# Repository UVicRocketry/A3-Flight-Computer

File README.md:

# A3-Flight-Computer
Hardware and software for Anduril-3 flight computer.

## Hardware 
All hardware is designed in KiCAD. If any footprints are added create a folder with the component name in the component-library folder and export all the files to there. when importing footprints and symbols add them to the A3-Flight-Computer library in KiCAD A3 Also add any datasheet and relevent documentation to this folder. 

## Software
All software will be stored in the A3-Flight-Computer-Software. (Rest of Organization TBD)

Various resources such as application notes, various datasheets etc will be stored in the resource folder

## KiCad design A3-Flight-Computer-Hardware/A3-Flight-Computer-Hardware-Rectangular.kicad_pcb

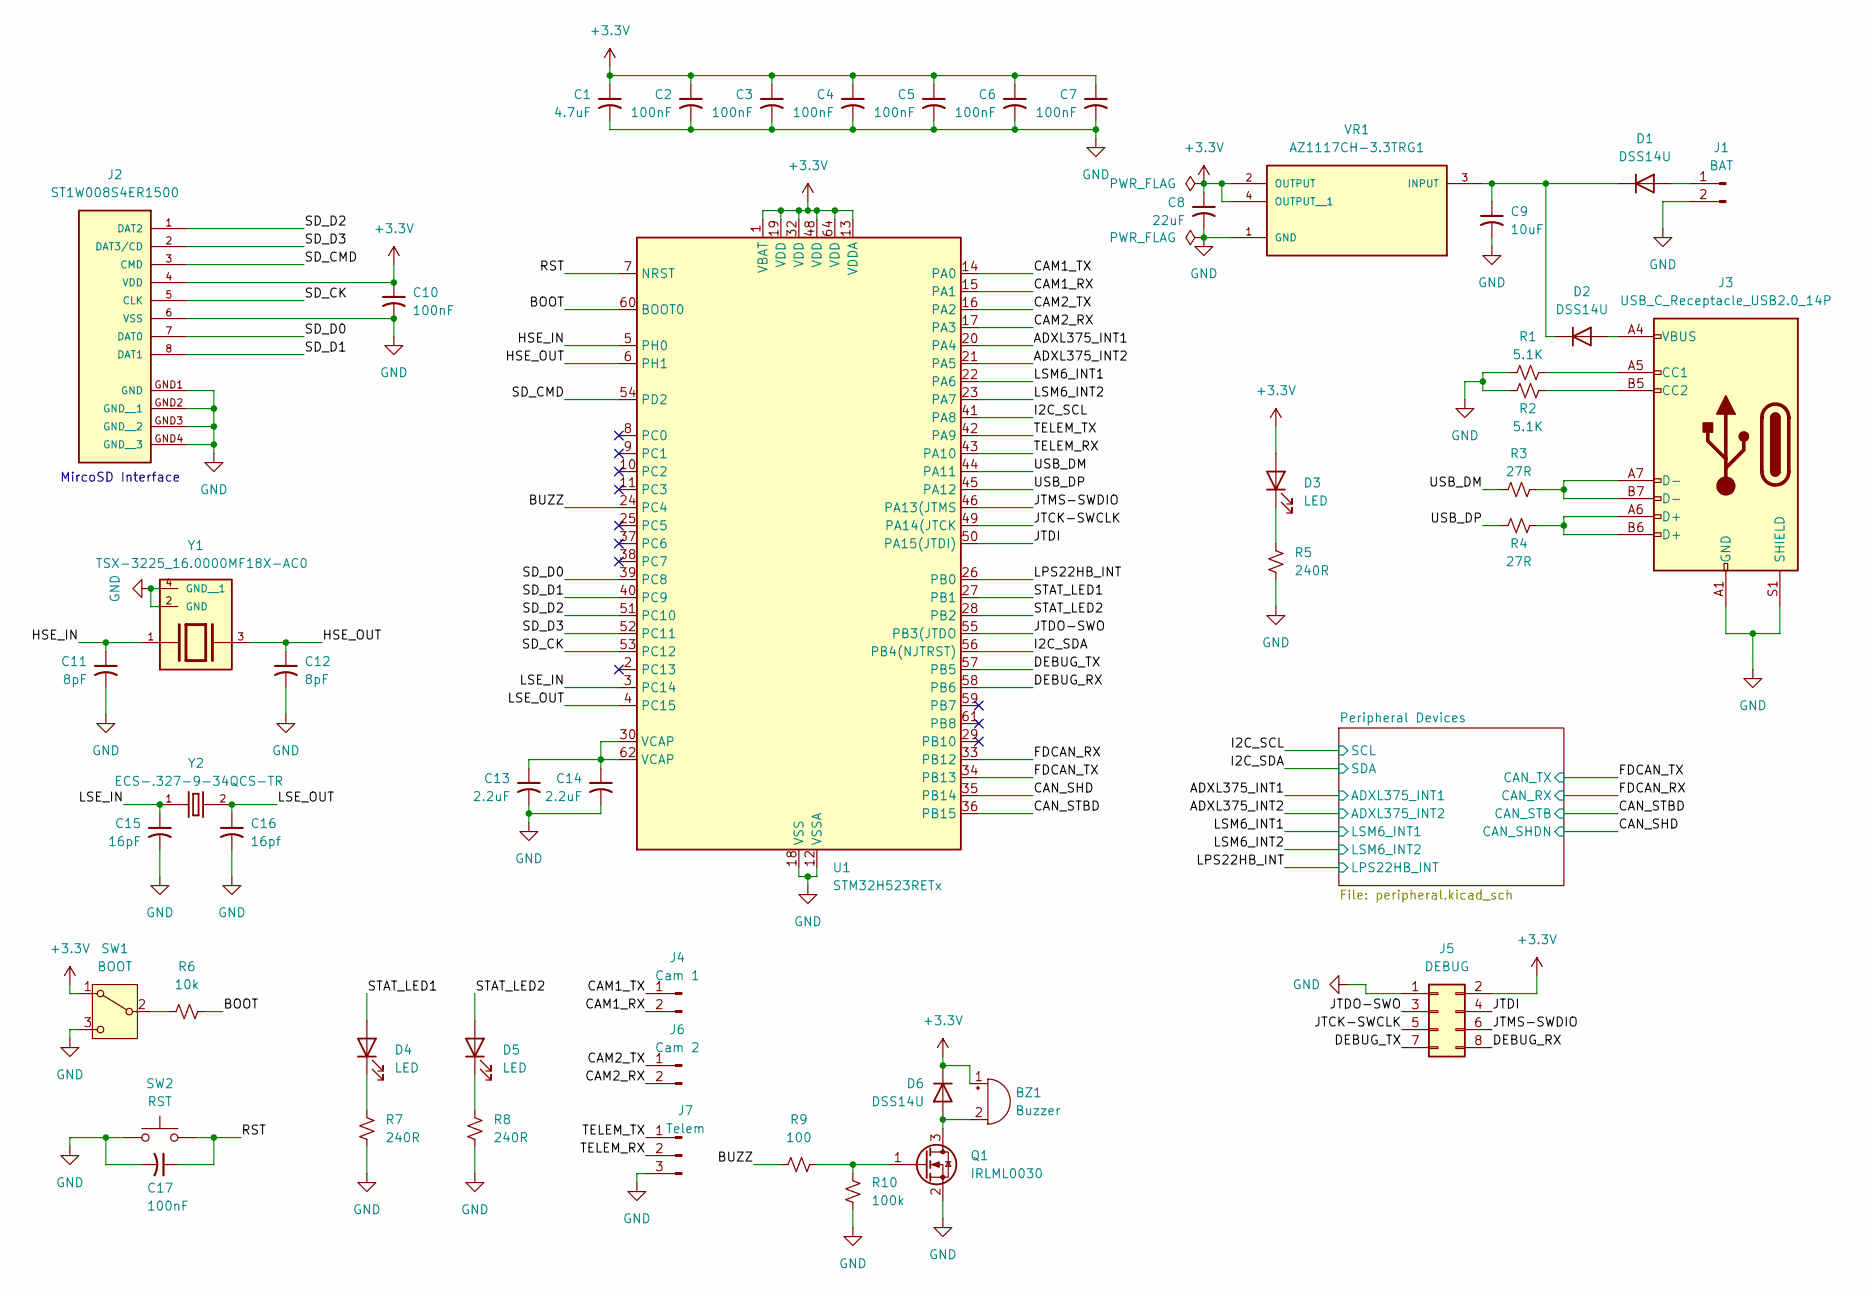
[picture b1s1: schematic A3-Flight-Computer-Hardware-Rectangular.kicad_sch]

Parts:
BZ1: Buzzer; Buzzer_Murata_PKMCS0909E
C1: 4.7uF; C_0805_2012Metric
C2, C3, C4, C5, C6, C7, C10, C17: 100nF; C_0402_1005Metric
C8: 22uF; C_0805_2012Metric
C9: 10uF; C_0805_2012Metric
C11, C12: 8pF; C_0402_1005Metric
C13, C14: 2.2uF; C_0402_1005Metric
C15: 16pF; C_0402_1005Metric
C16: 16pf; C_0402_1005Metric
D1, D2, D6: DSS14U; D_SOD-123
D3, D4, D5: LED; LED_0805_2012Metric_Pad1.15x1.40mm_HandSolder
J1: BAT; JST_XH_S2B-XH-A_1x02_P2.50mm_Horizontal
J2: ST1W008S4ER1500; JAE_ST1W008S4ER1500; PARTREV 2
J3: USB_C_Receptacle_USB2.0_14P; USB_C_Receptacle_Palconn_UTC16-G
J4: Cam 1; JST_XH_S2B-XH-A_1x02_P2.50mm_Horizontal
J5: DEBUG; PinHeader_2x04_P2.54mm_Vertical
J6: Cam 2; JST_XH_S2B-XH-A_1x02_P2.50mm_Horizontal
J7: Telem; JST_XH_S3B-XH-A_1x03_P2.50mm_Horizontal
Q1: IRLML0030; SOT-23
R1, R2: 5.1K; R_0402_1005Metric
R3, R4: 27R; R_0402_1005Metric
R5, R7, R8: 240R; R_0402_1005Metric
R6: 10k; R_0402_1005Metric
R9: 100; R_0402_1005Metric
R10: 100k; R_0402_1005Metric
SW1: BOOT; SW_SPDT_CK_JS102011SAQN
SW2: RST; SW_SPST_TS-1088-xR025
U1: STM32H523RETx; LQFP-64_10x10mm_P0.5mm
VR1: AZ1117CH-3.3TRG1; VREG_AZ1117CH-3.3TRG1; PARTREV 5 - 2
Y1: TSX-3225_16.0000MF18X-AC0; XTAL_TSX-3225_16.0000MF18X-AC0; PARTREV N/A
Y2: ECS-.327-9-34QCS-TR; XTAL_ECS-.327-9-34QCS-TR; PARTREV 2018

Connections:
+3.3V: BZ1.1 (+), C1.1, C2.1, C3.1, C4.1, C5.1, C6.1, C7.1, C8.1, C10.1, D3.2 (A), D6.1 (K), J2.4 (VDD), J5.2, SW1.1 (A), U1.1 (VBAT), U1.13 (VDDA), U1.19 (VDD), U1.32 (VDD), U1.48 (VDD), U1.64 (VDD), VR1.2 (OUTPUT), VR1.4 (OUTPUT__1); also elsewhere on the board
/ADXL375_INT1: U1.20 (PA4); also elsewhere on the board
/ADXL375_INT2: U1.21 (PA5); also elsewhere on the board
/BOOT: R6.2, U1.60 (BOOT0)
/BUZZ: R9.1, U1.24 (PC4)
/CAM1_RX: J4.2, U1.15 (PA1)
/CAM1_TX: J4.1, U1.14 (PA0)
/CAM2_RX: J6.2, U1.17 (PA3)
/CAM2_TX: J6.1, U1.16 (PA2)
/CAN_SHD: U1.35 (PB14); also elsewhere on the board
/CAN_STBD: U1.36 (PB15); also elsewhere on the board
/DEBUG_RX: J5.8, U1.58 (PB6)
/DEBUG_TX: J5.7, U1.57 (PB5)
/FDCAN_RX: U1.33 (PB12); also elsewhere on the board
/FDCAN_TX: U1.34 (PB13); also elsewhere on the board
/HSE_IN: C11.1, U1.5 (PH0), Y1.1
/HSE_OUT: C12.1, U1.6 (PH1), Y1.3
/I2C_SCL: U1.41 (PA8); also elsewhere on the board
/I2C_SDA: U1.56 (PB4(NJTRST)); also elsewhere on the board
/JTCK-SWCLK: J5.5, U1.49 (PA14(JTCK)
/JTDI: J5.4, U1.50 (PA15(JTDI))
/JTDO-SWO: J5.3, U1.55 (PB3(JTDO)
/JTMS-SWDIO: J5.6, U1.46 (PA13(JTMS)
/LPS22HB_INT: U1.26 (PB0); also elsewhere on the board
/LSE_IN: C15.1, U1.3 (PC14), Y2.1
/LSE_OUT: C16.1, U1.4 (PC15), Y2.2
/LSM6_INT1: U1.22 (PA6); also elsewhere on the board
/LSM6_INT2: U1.23 (PA7); also elsewhere on the board
/RST: C17.1, SW2.2, U1.7 (NRST)
/SD_CK: J2.5 (CLK), U1.53 (PC12)
/SD_CMD: J2.3 (CMD), U1.54 (PD2)
/SD_D0: J2.7 (DAT0), U1.39 (PC8)
/SD_D1: J2.8 (DAT1), U1.40 (PC9)
/SD_D2: J2.1 (DAT2), U1.51 (PC10)
/SD_D3: J2.2 (DAT3/CD), U1.52 (PC11)
/STAT_LED1: D4.2 (A), U1.27 (PB1)
/STAT_LED2: D5.2 (A), U1.28 (PB2)
/TELEM_RX: J7.2, U1.43 (PA10)
/TELEM_TX: J7.1, U1.42 (PA9)
/USB_DM: R3.1, U1.44 (PA11)
/USB_DP: R4.1, U1.45 (PA12)
GND: C1.2, C2.2, C3.2, C4.2, C5.2, C6.2, C7.2, C8.2, C9.2, C10.2, C11.2, C12.2, C13.2, C14.2, C15.2, C16.2, C17.2, J1.2, J2.6 (VSS), J2.GND1 (GND), J2.GND2 (GND__1), J2.GND3 (GND__2), J2.GND4 (GND__3), J3.A1 (GND), J3.A12 (GND), J3.B1 (GND), J3.B12 (GND), J3.S1 (SHIELD), J5.1, J7.3, Q1.2 (S), R1.1, R2.1, R5.1, R7.1, R8.1, R10.1, SW1.3 (C), SW2.1, U1.12 (VSSA), U1.18 (VSS), U1.31 (VSS), U1.47 (VSS), U1.63 (VSS), VR1.1 (GND), Y1.2 (GND), Y1.4 (GND__1); also elsewhere on the board
unnamed: BZ1.2 (-), D6.2 (A), Q1.3 (D)
unnamed: C13.1, C14.1, U1.30 (VCAP), U1.62 (VCAP)
unnamed: D1.2 (A), J1.1
unnamed: C9.1, D1.1 (K), D2.1 (K), VR1.3 (INPUT)
unnamed: D2.2 (A), J3.A4 (VBUS), J3.A9 (VBUS), J3.B4 (VBUS), J3.B9 (VBUS)
unnamed: D3.1 (K), R5.2
unnamed: D4.1 (K), R7.2
unnamed: D5.1 (K), R8.2
unnamed: J3.A5 (CC1), R1.2
unnamed: J3.B5 (CC2), R2.2
unnamed: J3.A6 (D+), J3.B6 (D+), R4.2
unnamed: J3.A7 (D-), J3.B7 (D-), R3.2
unnamed: Q1.1 (G), R9.2, R10.2
unnamed: R6.1, SW1.2 (B)

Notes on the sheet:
MircoSD Interface

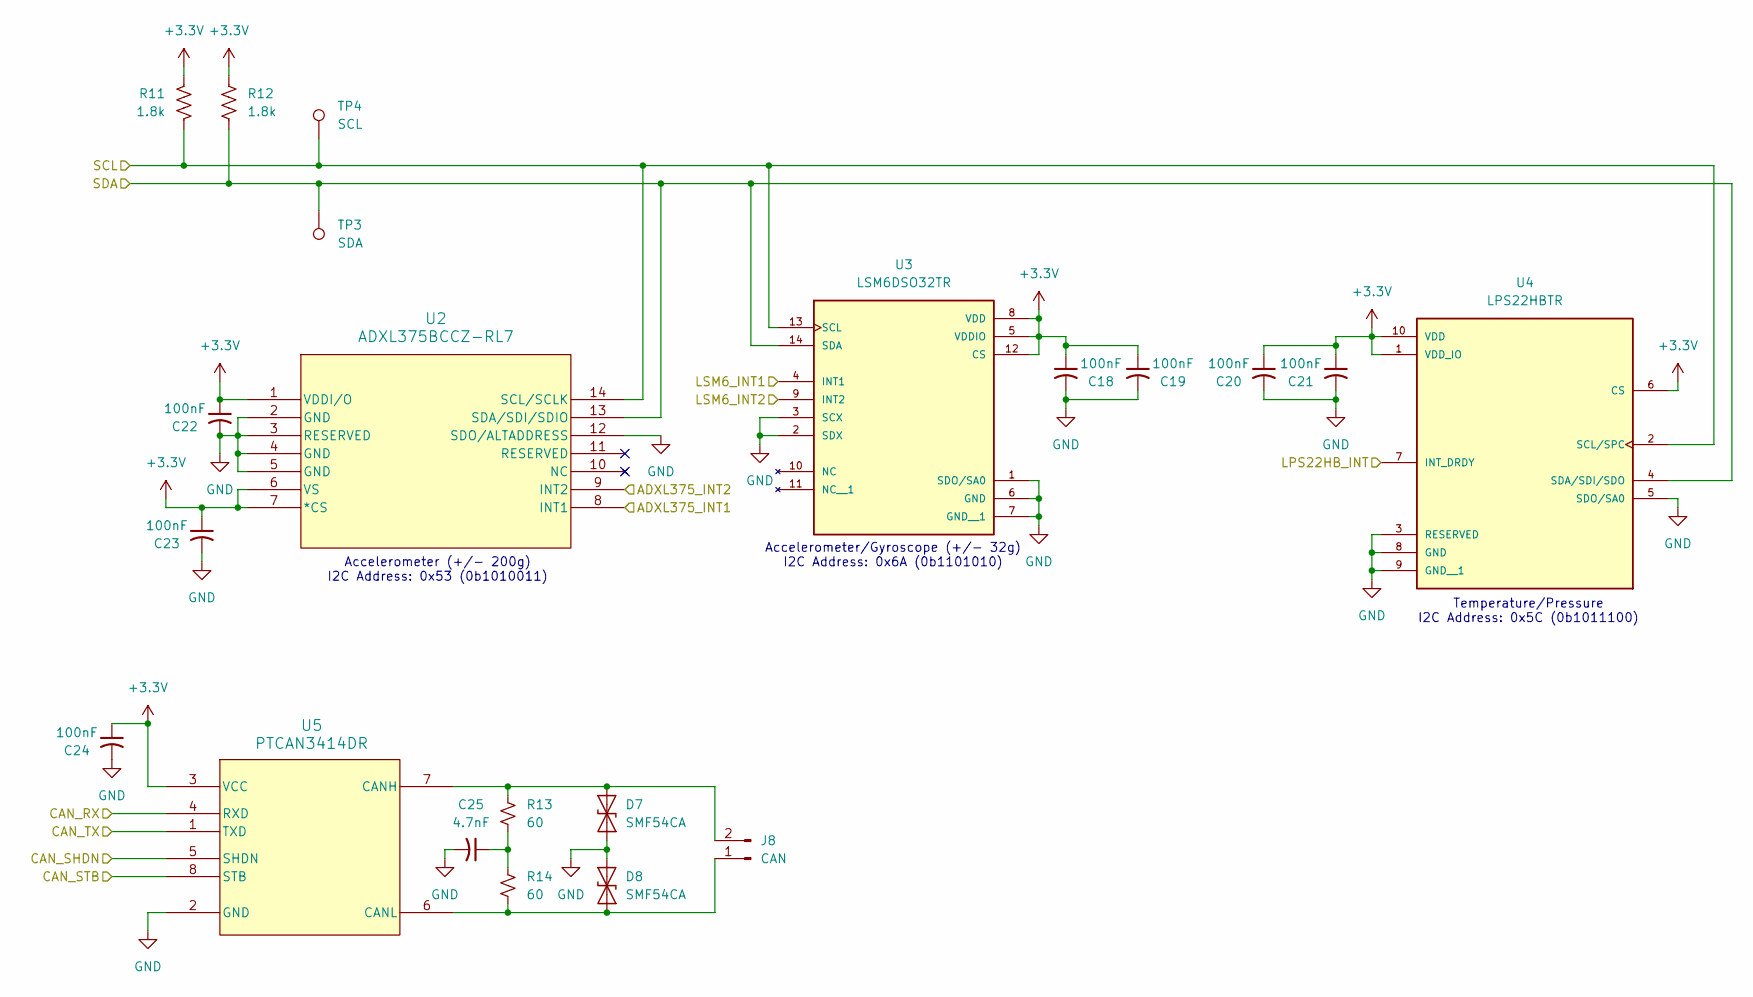
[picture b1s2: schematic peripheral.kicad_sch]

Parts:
C18, C19, C20, C21, C22, C23, C24: 100nF; C_0402_1005Metric
C25: 4.7nF; C_0402_1005Metric
D7, D8: SMF54CA; D_SMF
J8: CAN; JST_XH_S2B-XH-A_1x02_P2.50mm_Horizontal
R11, R12: 1.8k; R_0402_1005Metric
R13, R14: 60; R_0402_1005Metric
TP3: SDA; TestPoint_THTPad_1.0x1.0mm_Drill0.5mm
TP4: SCL; TestPoint_THTPad_1.0x1.0mm_Drill0.5mm
U2: ADXL375BCCZ-RL7; LGA_CC-14-1_ADI
U3: LSM6DSO32TR; XDCR_LSM6DSO32TR; PARTREV 1
U4: LPS22HBTR; PQFN50P200X200X80-10N; PARTREV 6
U5: PTCAN3414DR; SOIC8_D_TEX

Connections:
+3.3V: C18.1, C19.1, C20.1, C21.1, C22.1, C23.1, C24.1, R11.1, R12.1, U2.1 (VDDI/O), U2.6 (VS), U2.7 (*CS), U3.5 (VDDIO), U3.8 (VDD), U3.12 (CS), U4.1 (VDD_IO), U4.6 (CS), U4.10 (VDD), U5.3 (VCC); also elsewhere on the board
/ADXL375_INT1: U2.8 (INT1); also elsewhere on the board
/ADXL375_INT2: U2.9 (INT2); also elsewhere on the board
/CAN_SHD: U5.5 (SHDN); also elsewhere on the board
/CAN_STBD: U5.8 (STB); also elsewhere on the board
/FDCAN_RX: U5.4 (RXD); also elsewhere on the board
/FDCAN_TX: U5.1 (TXD); also elsewhere on the board
/I2C_SCL: R11.2, TP4.1, U2.14 (SCL/SCLK), U3.13 (SCL), U4.2 (SCL/SPC); also elsewhere on the board
/I2C_SDA: R12.2, TP3.1, U2.13 (SDA/SDI/SDIO), U3.14 (SDA), U4.4 (SDA/SDI/SDO); also elsewhere on the board
/LPS22HB_INT: U4.7 (INT_DRDY); also elsewhere on the board
/LSM6_INT1: U3.4 (INT1); also elsewhere on the board
/LSM6_INT2: U3.9 (INT2); also elsewhere on the board
GND: C18.2, C19.2, C20.2, C21.2, C22.2, C23.2, C24.2, C25.2, D7.2 (A2), D8.1 (A1), U2.2 (GND), U2.3 (RESERVED), U2.4 (GND), U2.5 (GND), U2.12 (SDO/ALTADDRESS), U3.1 (SDO/SA0), U3.2 (SDX), U3.3 (SCX), U3.6 (GND), U3.7 (GND__1), U4.3 (RESERVED), U4.5 (SDO/SA0), U4.8 (GND), U4.9 (GND__1), U5.2 (GND); also elsewhere on the board
unnamed: C25.1, R13.1, R14.2
unnamed: D7.1 (A1), J8.2, R13.2, U5.7 (CANH)
unnamed: D8.2 (A2), J8.1, R14.1, U5.6 (CANL)

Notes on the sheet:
Accelerometer (+/- 200g) I2C Address: 0x53 (0b1010011)
Temperature/Pressure I2C Address: 0x5C (0b1011100)
Accelerometer/Gyroscope (+/- 32g) I2C Address: 0x6A (0b1101010)

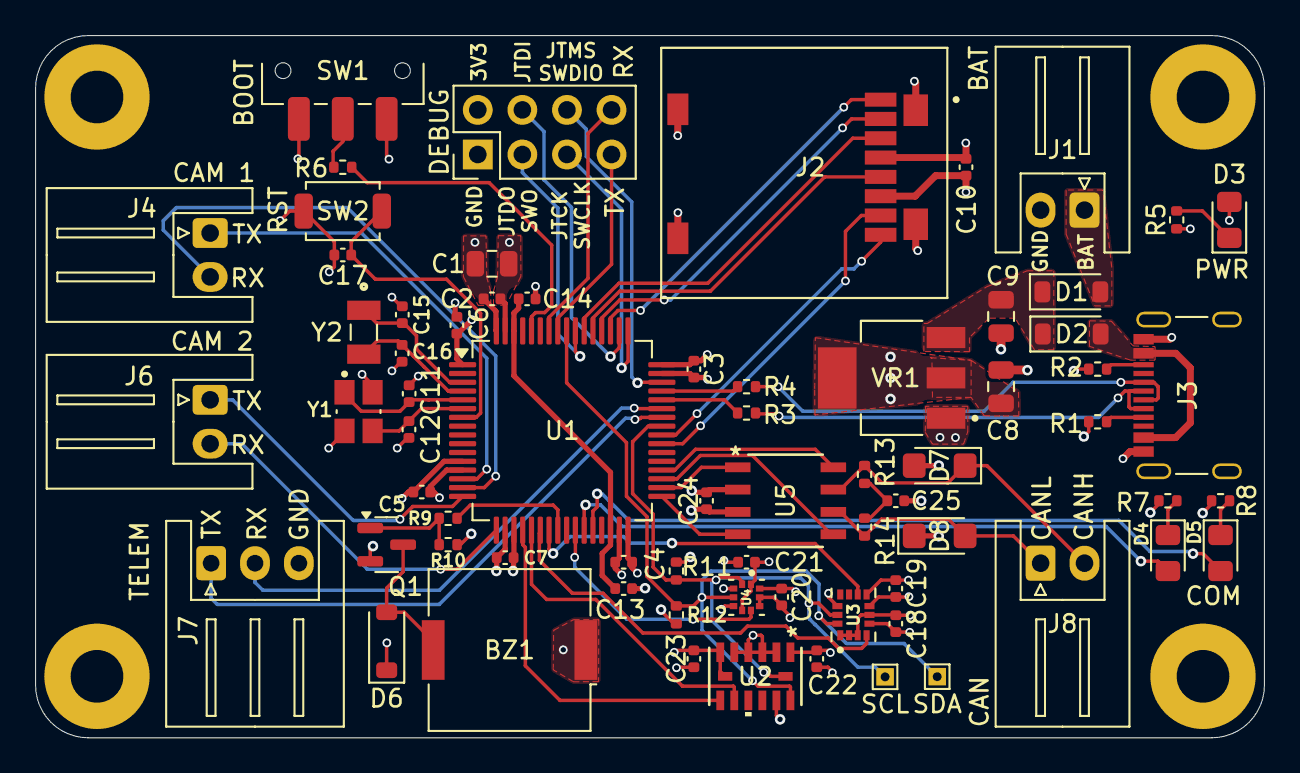
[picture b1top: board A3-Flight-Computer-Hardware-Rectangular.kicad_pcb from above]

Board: 4 copper layers, 70.0 x 40.0 mm, 69 parts (0 on the bottom side), 59 nets.

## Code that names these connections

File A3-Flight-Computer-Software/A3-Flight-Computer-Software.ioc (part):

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Mcu.Name=STM32H523RETx
Mcu.Package=LQFP64
Mcu.UserName=STM32H523RETx
PA10.Signal=USART1_RX
PA11.Mode=Device
PA11.Signal=USB_DM
PA12.Mode=Device
PA12.Signal=USB_DP
PA13(JTMS/SWDIO).Mode=JTAG_4_pins
PA13(JTMS/SWDIO).Signal=DEBUG_JTMS-SWDIO
PA14(JTCK/SWCLK).Mode=JTAG_4_pins
PA14(JTCK/SWCLK).Signal=DEBUG_JTCK-SWCLK
PA15(JTDI).Mode=JTAG_4_pins
PA15(JTDI).Signal=DEBUG_JTDI
PA4.Signal=GPXTI4
PA5.Signal=GPXTI5
PA6.Signal=GPXTI6
PA7.Signal=GPXTI7
PA8.Mode=I2C
PA8.Signal=I2C3_SCL
PA9.Signal=USART1_TX
PB0.Signal=GPXTI0
PB1.Signal=GPIO_Output
PB12.Mode=FDCAN_Activate
PB12.Signal=FDCAN2_RX
PB13.Mode=FDCAN_Activate
PB13.Signal=FDCAN2_TX
PB14.Signal=GPIO_Output
PB15.Signal=GPIO_Output
PB2.Signal=GPIO_Output
PB3(JTDO/TRACESWO).Mode=JTAG_4_pins
PB3(JTDO/TRACESWO).Signal=DEBUG_JTDO-SWO
PB4(NJTRST).Mode=I2C
PB4(NJTRST).Signal=I2C3_SDA
PB5.Signal=UART5_RX
PB6.Signal=UART5_TX
PC10.GPIOParameters=GPIO_PuPd
PC10.GPIO_PuPd=GPIO_PULLUP
PC10.Mode=SD_4_bits_Wide_bus
PC10.Signal=SDMMC1_D2
PC11.GPIOParameters=GPIO_PuPd
PC11.GPIO_PuPd=GPIO_PULLUP
PC11.Mode=SD_4_bits_Wide_bus
PC11.Signal=SDMMC1_D3
PC12.GPIOParameters=GPIO_PuPd
PC12.GPIO_PuPd=GPIO_NOPULL
PC12.Mode=SD_4_bits_Wide_bus
PC12.Signal=SDMMC1_CK
PC13.Mode=Timestamp enabled
PC13.Signal=RTC_TS
PC14-OSC32_IN(OSC32_IN).Mode=LSE-External-Oscillator
PC14-OSC32_IN(OSC32_IN).Signal=RCC_OSC32_IN
PC15-OSC32_OUT(OSC32_OUT).Mode=LSE-External-Oscillator
PC15-OSC32_OUT(OSC32_OUT).Signal=RCC_OSC32_OUT
PC4.Signal=S_TIM2_CH4
PC8.GPIOParameters=GPIO_PuPd
PC8.GPIO_PuPd=GPIO_PULLUP
PC8.Mode=SD_4_bits_Wide_bus
PC8.Signal=SDMMC1_D0
PC9.GPIOParameters=GPIO_PuPd
PC9.GPIO_PuPd=GPIO_PULLUP
PC9.Mode=SD_4_bits_Wide_bus
PC9.Signal=SDMMC1_D1
PD2.GPIOParameters=GPIO_PuPd
PD2.GPIO_PuPd=GPIO_PULLUP
PD2.Mode=SD_4_bits_Wide_bus
PD2.Signal=SDMMC1_CMD
PH0-OSC_IN(PH0).Mode=HSE-External-Oscillator
PH0-OSC_IN(PH0).Signal=RCC_OSC_IN
PH1-OSC_OUT(PH1).Mode=HSE-External-Oscillator
PH1-OSC_OUT(PH1).Signal=RCC_OSC_OUT
RCC.HSE_VALUE=16000000
RCC.SYSCLKFreq_VALUE=250000000
RCC.SYSCLKSource=RCC_SYSCLKSOURCE_PLLCLK
board=custom

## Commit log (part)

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2025-10-24 Expand README with hardware and software sections
    Added sections for hardware and software details.
2025-10-24 Initial Repository Setup
2025-10-29 Initial schematic
2025-11-04 First PCB revision
2025-11-09 Adjusted PCB Dimensions
2025-11-20 Small routing changes
2025-12-07 Added labels and changed component sizes
2026-01-13 Updated gerber files + BOM for purchasing
2026-05-20 Updated STM32CubeMX board Config
2026-05-28 Added FatFs driver
2026-06-20 Updated board and setup cmake files
2026-06-25 Added Callback and FS Init
2026-06-27 Added basic accelerometer drivers and RTC configuration
